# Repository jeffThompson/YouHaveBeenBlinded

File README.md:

# You Have Been Blinded
A non-visual, haptic electronic game developed in collaboration with Alex Myers.

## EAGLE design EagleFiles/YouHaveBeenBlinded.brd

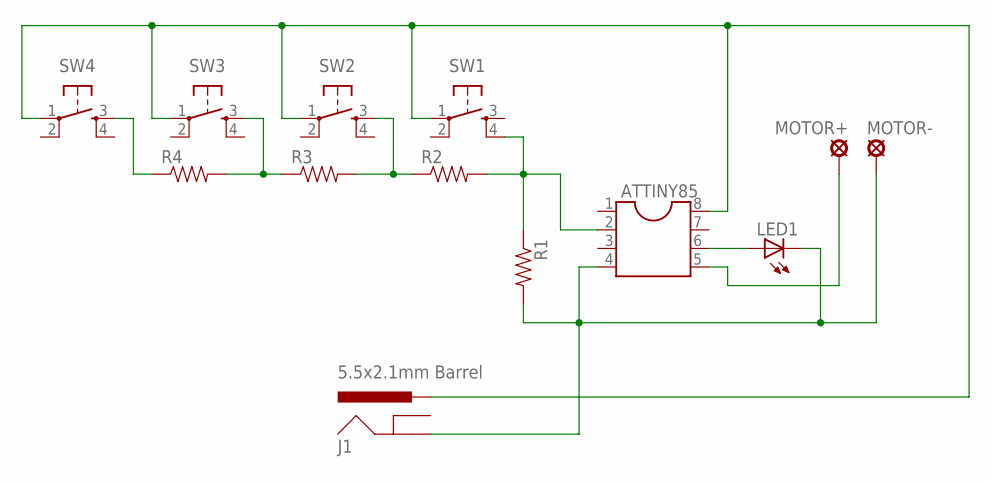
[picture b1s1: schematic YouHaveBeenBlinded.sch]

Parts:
ATTINY85: DIL8S; SOCKET-08
J1: 5.5x2.1mm Barrel; POWER_JACK_SMD
LED1: LEDCHIPLED_0805; CHIPLED_0805
MOTOR+: LSP10
MOTOR-: LSP10
R1, R2, R3, R4: RESISTOR2010; R2010
SW1, SW2, SW3, SW4: TAC_SWITCHPTH; TACTILE-PTH

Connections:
+3V: ATTINY85.8, J1.VIN0 (PWR), SW1.1, SW2.1, SW3.1, SW4.1
GND: ATTINY85.4, J1.P$4 (GND), LED1.C, MOTOR-.MP, R1.2
unnamed: ATTINY85.5, MOTOR+.MP
unnamed: ATTINY85.2, R1.1, R2.2, SW1.4
unnamed: ATTINY85.6, LED1.A
unnamed: R4.1, SW4.3
unnamed: R3.1, R4.2, SW3.3
unnamed: R2.1, R3.2, SW2.3

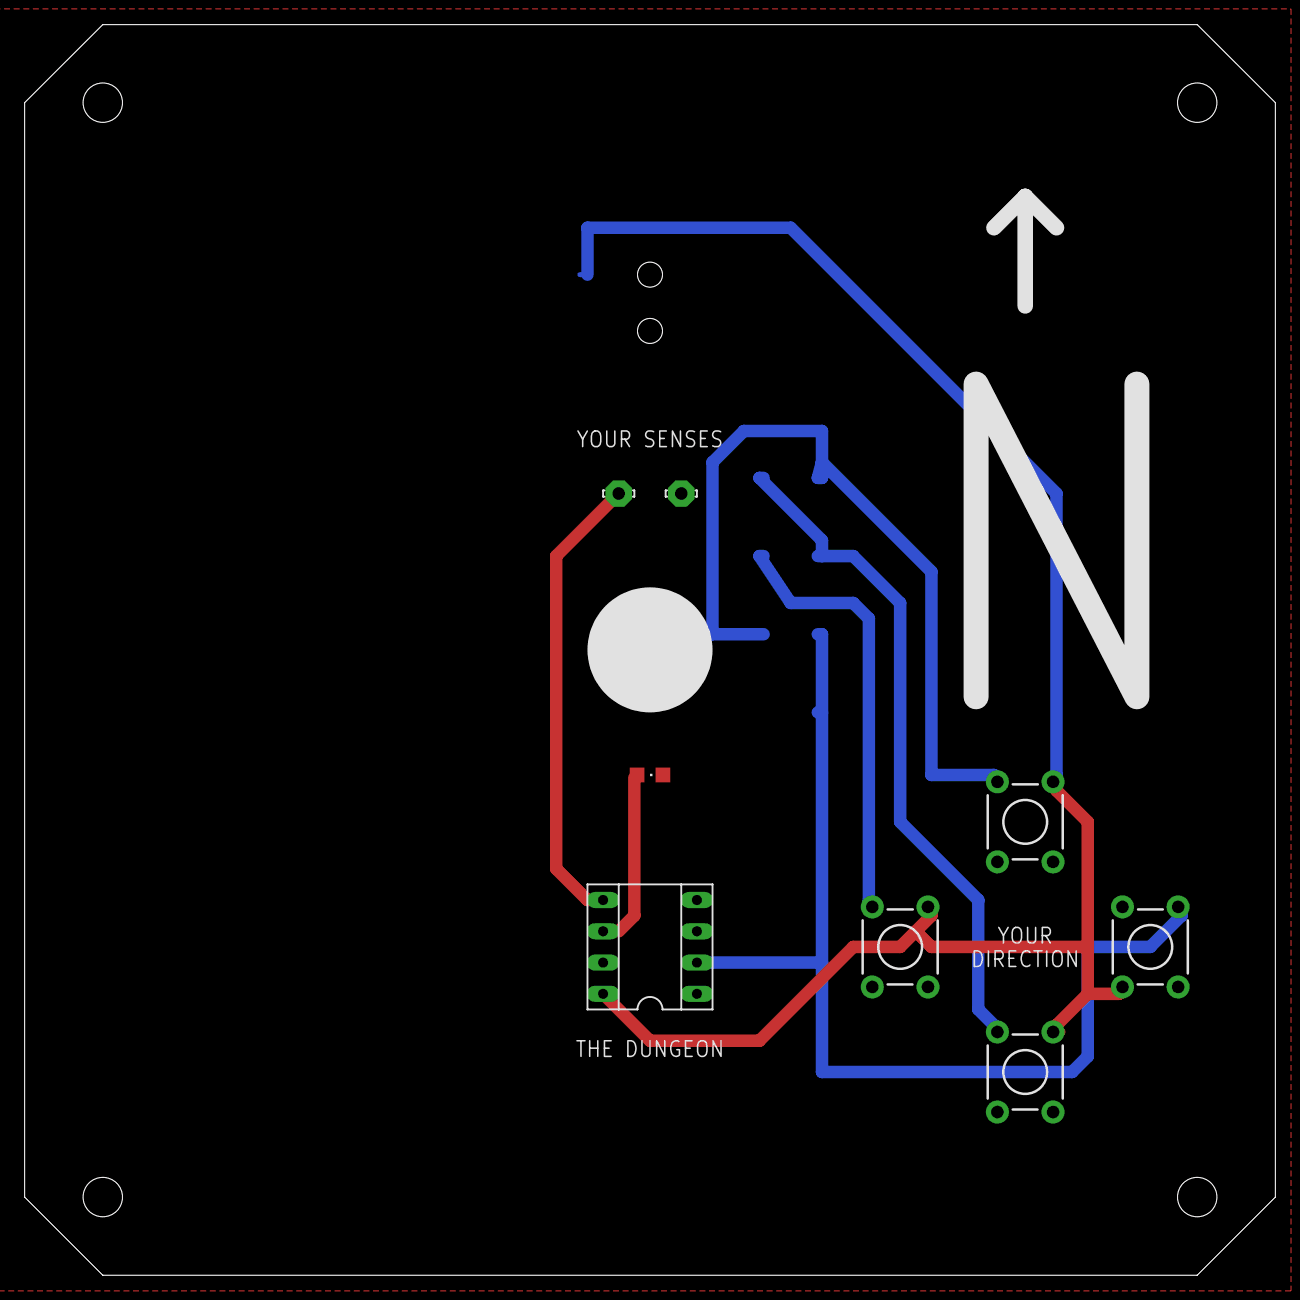
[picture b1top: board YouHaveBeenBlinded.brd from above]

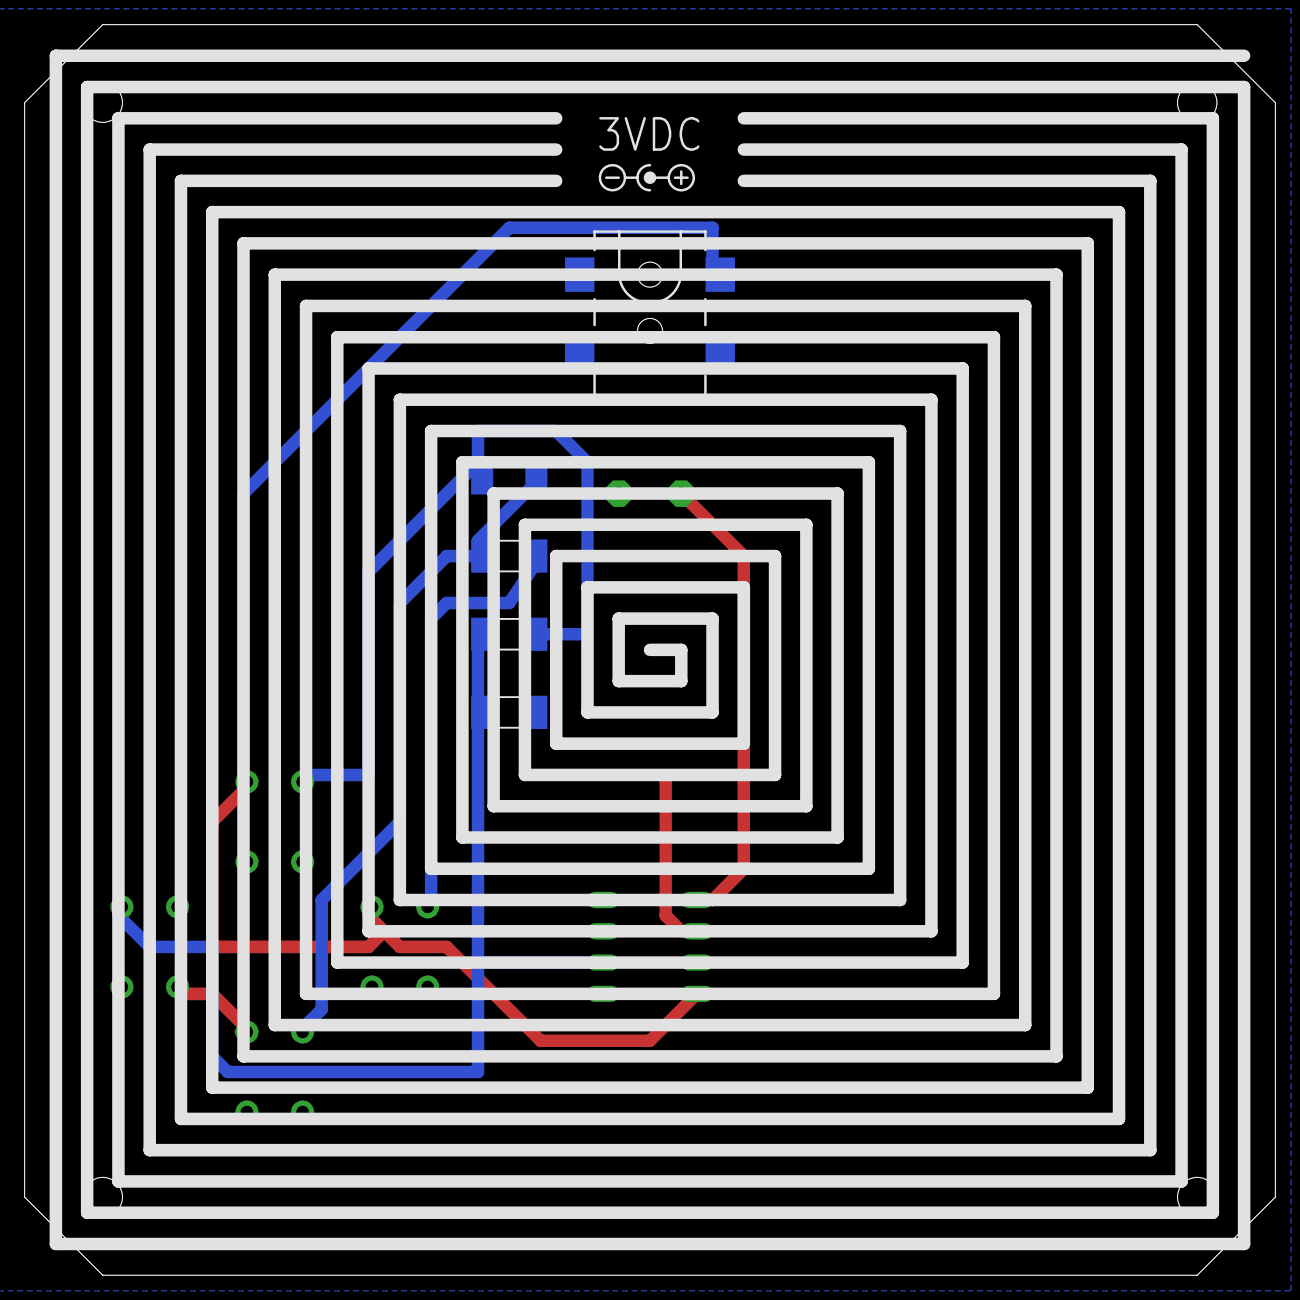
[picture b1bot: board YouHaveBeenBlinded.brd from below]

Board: 2 copper layers, 101.6 x 101.6 mm, 13 parts (5 on the bottom side), 8 nets.

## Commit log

2015-10-14 Code cleanup for ATtiny85
2015-10-14 Updated parts list
2015-10-14 Etched braille instead
2015-10-14 Final release of Eagle and Gerber files
2015-10-14 Updated pushbutton part #
2015-10-14 Created Levels folder with Level 1
    Level1.psd added to /Levels
2015-10-14 LED brightness tweaks
2015-10-14 Updated level converter util
2015-10-14 Old levels, for posterity
2015-10-14 New level files
2015-10-14 Testing converter script
2015-10-14 PNG version of level for converter
2015-10-14 Made changes to Level 1
2015-10-15 Final level files
2015-10-15 Updated code with final level layout
2015-10-15 Added auto-output of start position

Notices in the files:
parts and their libraries:
SparkFun-Connectors: Licensing: Creative Commons ShareAlike 4.0 International - https://creativecommons.org/licenses/by-sa/4.0
